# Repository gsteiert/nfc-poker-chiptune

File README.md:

# NFC POKER CHIPTUNE
# A noisy poker chip with a message to share

This board is the pinnacle of my beeping businesscard project.  It is a pocketable version in the dimmensions of a real poker chip.  It has an engergy harvesting NFC EEPROM and WCH CH32V003 MCU.  The MCU is connected to an LED and piezo buzzer.  The two ICs are 8 pin SOIC, and the passives are 0603 so it is not too dificult to hand assemble.

3D files are provided for a snap on poker chip frame.  The design is in three pieces to allow two color with no supports to remove.  The three pieces all fit together securely when snapped around the pcb.

The MCU is connected to the NFC EEPROM via I2C and it reads the memory starting at NFC page 0x20 for the encoded tune, so the tune can be written and updated over NFC.

This board uses the NXP NT3H2211 or NT3H2111 for the energy harvesting tag.  I chose this device after [building a battle board to characterize the output power](https://hackaday.io/project/177897-beeping-blinking-business-card-badge-b4/log/221626-course-correction) of this versus the ST25DV.  The NXP part has better voltage regulation and maintains the voltage better under load.  You can see [the results in a hackaday project log](https://hackaday.io/project/177897-beeping-blinking-business-card-badge-b4/log/221646-power-estimates).

## Board Variations

The nfc-coin.kicad_pcb file has a simplified 2 color version of the logo in front silkscreen.
The nfc-coin-enig.kicad_pcb file has a 3 color version of the logo that looks better with ENIG finish and a dark soldermask like is offered by [OSH Park](https://oshpark.com/) 

## Building the code

The MCU firmware is built using an older version of [ch32fun](https://github.com/cnlohr/ch32fun/tree/v0.9)  You need to clone this repo separately and may need to update the relative path in the Makefile.

## NFC Programming

You can format the NFC tag and load a URL that will be shared when tapped using the NXP TagWriter Android app.  (there may be an iPhone version, but I have not used it)  You can also store other data like VCARDs, but iPhones are very particular about which NFC messages they will read and it is safer to use URLs.

The NXP TagWriter app does not work well with binary data, so I recommned the ST25 Android app for writing the binary coded tune.  Be sure to write the binary file to the proper location, writing binary data to the wrong address can lock the tag and make it unusable.  Page 0x20 is address 0x200 in the app.

## Tune Format

The tune format is very simple.
A note is encoded in two bytes consisting of four nibles:

| Bits |  15-12      |  11-8      |  7-4   |  3-0 |
|:-----|:-----------:|:----------:|:-------|:----:|
| Data | Whole Notes | 1/16 Notes | Octave | Note |

Note values are:
C=0x0, C#=0x1, D=0x2, Eb=0x3, 
E=0x4, F=0x5, F#=0x6, G=0x7, 
G#=0x8, A=0x9, Bb=0xA, B=0xB, 
Rest=0xF

Whole Note count value of 0xF is a loop command that will go back to the note index encoded in the lower 8 bits (Octave and Note nibbles).  Add 0xF000 at the end of your tune to get it to repeat.

TBD:  There is no gap between notes, so two consecutive entries of the same note will string together.  A rest between notes should be added to the code.

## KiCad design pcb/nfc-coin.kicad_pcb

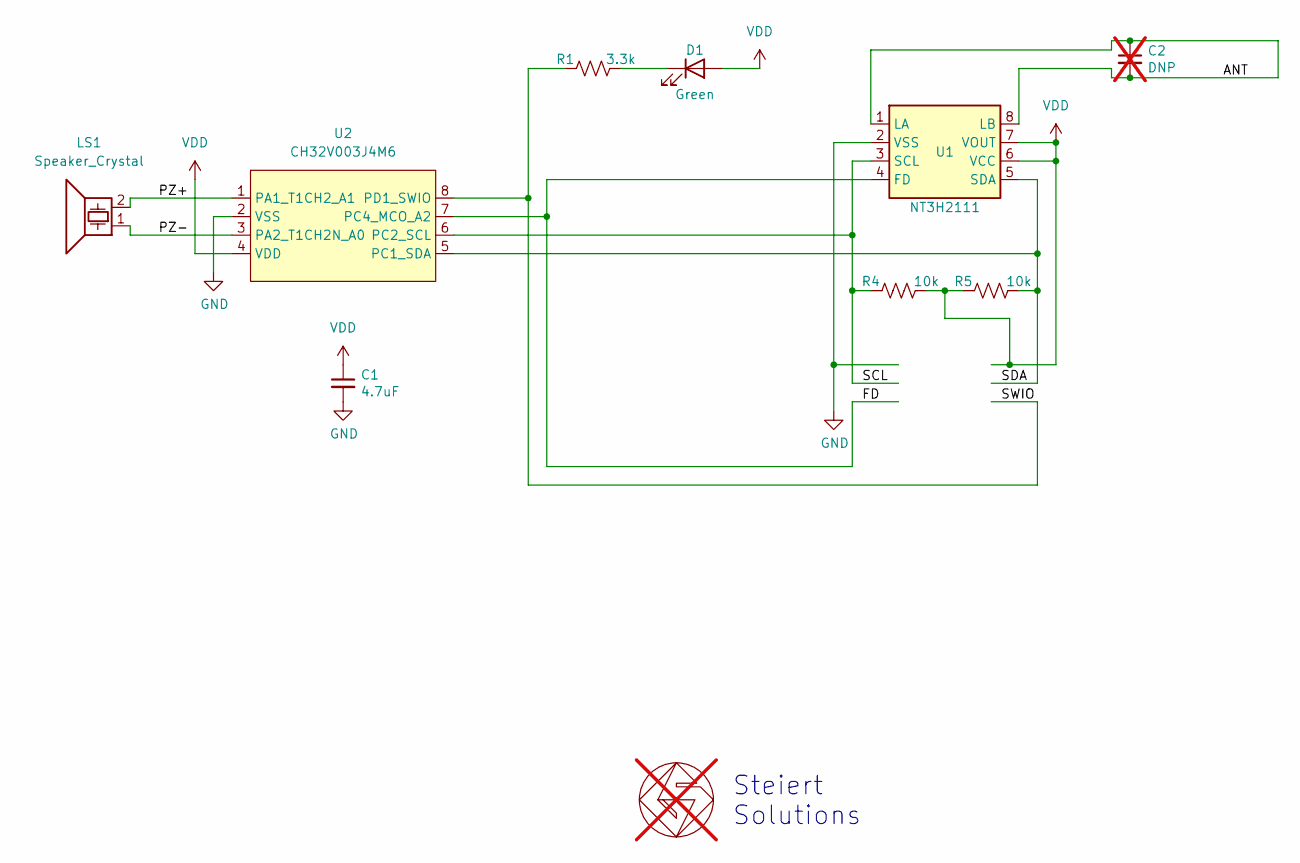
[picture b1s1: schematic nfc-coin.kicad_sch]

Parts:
C1: 4.7uF; C_0603_1608Metric_Pad1.08x0.95mm_HandSolder; MPN CL10A475KP8NNNC; LCSC C1705
C2: DNP; C_0603_1608Metric; not fitted
D1: Green; LED_0603_1608Metric_Pad1.05x0.95mm_HandSolder; MPN DYWH-19-21SUGC/4T; LCSC C47416536
GS1: GS_logo; gs_logo_200mil; not fitted
LS1: Speaker_Crystal; Buzzer_Mallory_AST1109MLTRQ; MPN FUET-1109; LCSC C391036
R1: 3.3k; R_0603_1608Metric_Pad0.98x0.95mm_HandSolder; MPN RC0603FR-073K3L; LCSC C108078
R4, R5: 10k; R_0603_1608Metric_Pad0.98x0.95mm_HandSolder; MPN RC0603FR-0710KL; LCSC C98220
U1: NT3H2111; SO-8_3.9x4.9mm_P1.27mm; MPN NT3H2111W0FT1X; LCSC C2654859
U2: CH32V003J4M6; SO-8_3.9x4.9mm_P1.27mm; MPN CH32V003J4M6; LCSC C5346354

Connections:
/ANT: C2.1, C2.2, U1.1 (LA), U1.8 (LB)
/FD: U1.4 (FD), U2.7 (PC4_MCO_A2)
/PZ+: LS1.2, U2.1 (PA1_T1CH2_A1)
/PZ-: LS1.1, U2.3 (PA2_T1CH2N_A0)
/SCL: R4.2, U1.3 (SCL), U2.6 (PC2_SCL)
/SDA: R5.1, U1.5 (SDA), U2.5 (PC1_SDA)
/SWIO: R1.2, U2.8 (PD1_SWIO)
GND: C1.2, U1.2 (VSS), U2.2 (VSS)
unnamed: D1.1 (K), R1.1
VDD: C1.1, D1.2 (A), R4.1, R5.2, U1.6 (VCC), U1.7 (VOUT), U2.4 (VDD)

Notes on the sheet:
Steiert Solutions

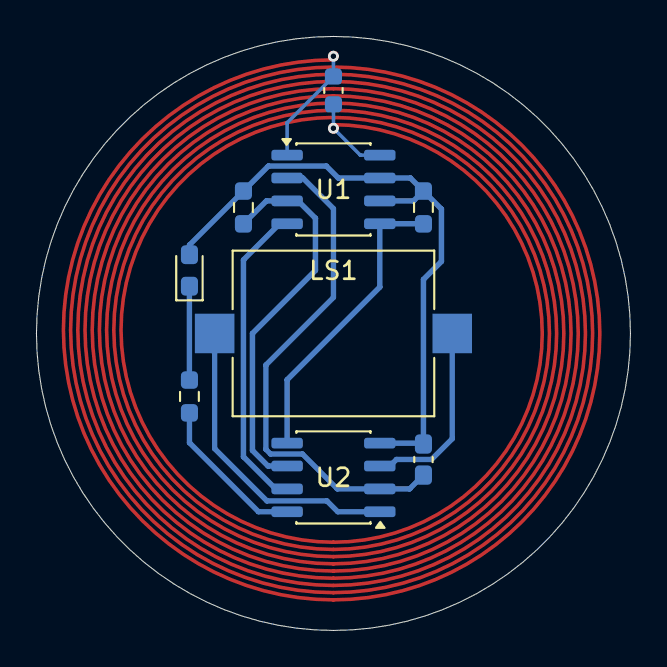
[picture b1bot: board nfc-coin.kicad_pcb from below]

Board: 2 copper layers, 33.0 x 33.0 mm, 9 parts (9 on the bottom side), 10 nets.
